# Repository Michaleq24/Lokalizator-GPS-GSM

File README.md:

Katalog zawiera dokumentację i pliki związane z projektem "Lokalizator GPS/GSM".

Autor: Michał Figołuszka  INF s.5 gr.2

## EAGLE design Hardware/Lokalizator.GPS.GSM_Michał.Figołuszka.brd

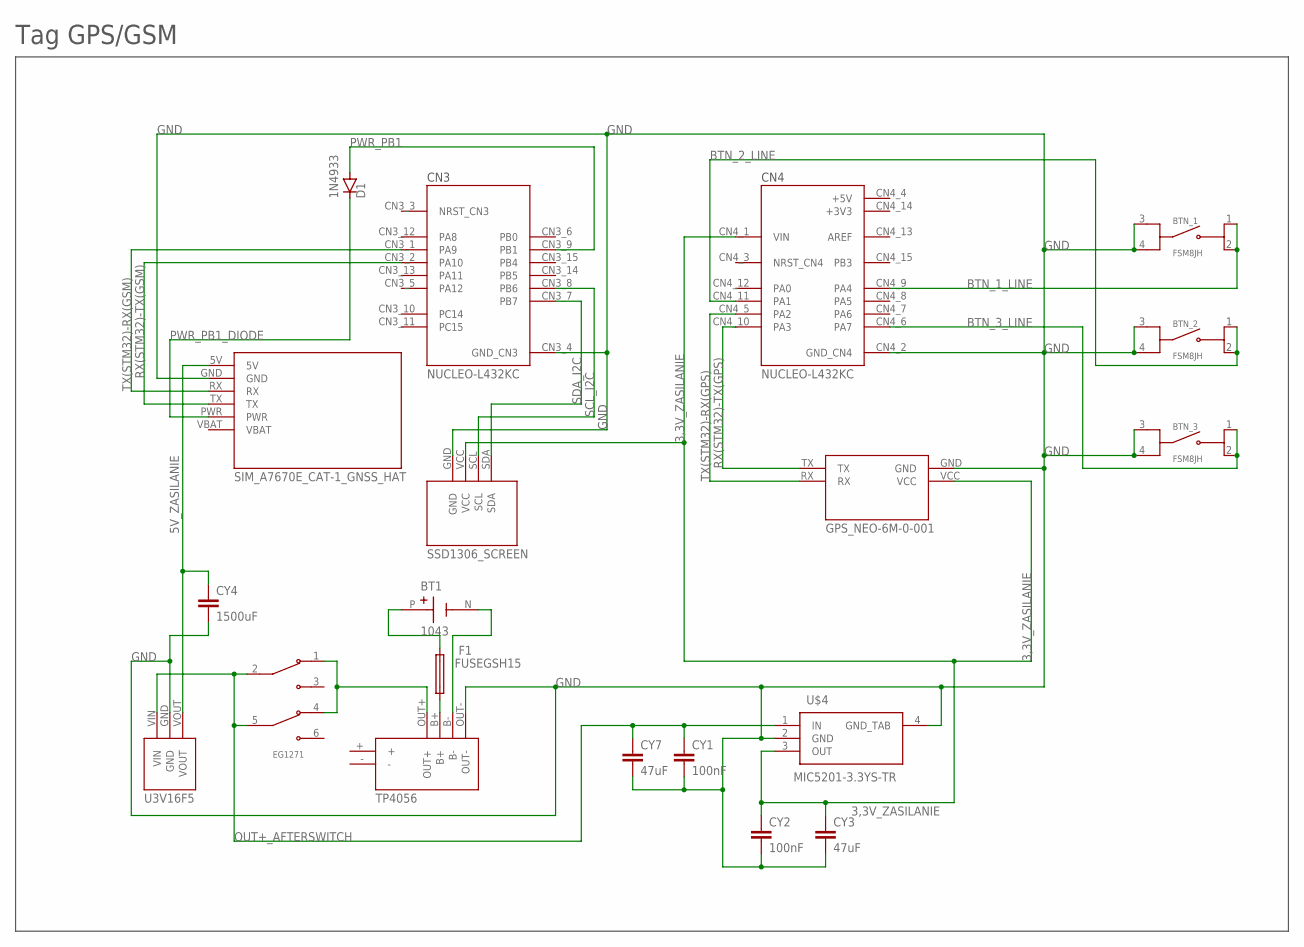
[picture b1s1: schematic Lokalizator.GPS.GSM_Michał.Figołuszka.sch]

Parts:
BT1: 1043; BAT_1043
BTN_1, BTN_2, BTN_3: FSM8JH; SW_FSM8JH
CY1, CY2: 100nF; YC7B5
CY3, CY7: 47uF; YC7B5
CY4: 1500uF; YC7B5
D1: 1N4933; DO41-10
F1: FUSEGSH15; GSH15
S1: EG1271; SW_EG1271
U1: NUCLEO-L432KC; MODULE_NUCLEO-L432KC
U$1: U3V16F5
U$2: TP4056
U$3: SSD1306_SCREEN
U$4: MIC5201-3.3YS-TR; SOT230P700X180-4N
U$6: SIM7020E_NB-IOT_HAT
U$7: GPS_NEO-6M-0-001

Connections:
3,3V_ZASILANIE: CY2.1, CY3.1, U1.CN4_1 (VIN), U$3.VCC, U$4.3 (OUT), U$7.VCC
5V_ZASILANIE: CY4.1, U$1.VOUT, U$6.5V
+3V3: U1.CN4_14 (+3V3)
+5V: U1.CN4_4 (+5V)
B+: BT1.P (POS), F1.2
B+_2: F1.1, U$2.B+
B-: BT1.N (NEG), U$2.B-
BTN_1_LINE: BTN_1.1 (NO_1), BTN_1.2 (NO_2), U1.CN4_9 (PA4)
BTN_2_LINE: BTN_2.1 (NO_1), BTN_2.2 (NO_2), U1.CN4_11 (PA1)
BTN_3_LINE: BTN_3.1 (NO_1), BTN_3.2 (NO_2), U1.CN4_6 (PA7)
GND: BTN_1.3 (COM_3), BTN_1.4 (COM_4), BTN_2.3 (COM_3), BTN_2.4 (COM_4), BTN_3.3 (COM_3), BTN_3.4 (COM_4), CY1.2, CY2.2, CY3.2, CY4.2, CY7.2, U1.CN3_4 (GND_CN3), U1.CN4_2 (GND_CN4), U$1.GND, U$2.OUT-, U$3.GND, U$4.2 (GND), U$4.4 (GND_TAB), U$6.GND, U$7.GND
OUT+: S1.1 (NC1), S1.4 (NC2), U$2.OUT+
OUT+_AFTERSWITCH: CY1.1, CY7.1, S1.2 (COM1), S1.5 (COM2), U$1.VIN, U$4.1 (IN)
PWR_PB1: D1.A, U1.CN3_9 (PB1)
PWR_PB1_DIODE: D1.C, U$6.PWR
RX(STM32)-TX(GPS): U1.CN4_10 (PA3), U$7.TX
RX(STM32)-TX(GSM): U1.CN3_2 (PA10), U$6.TX
SCL_I2C: U1.CN3_8 (PB6), U$3.SCL
SDA_I2C: U1.CN3_7 (PB7), U$3.SDA
TX(STM32)-RX(GPS): U1.CN4_5 (PA2), U$7.RX
TX(STM32)-RX(GSM): U1.CN3_1 (PA9), U$6.RX

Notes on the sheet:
Tag GPS/GSM

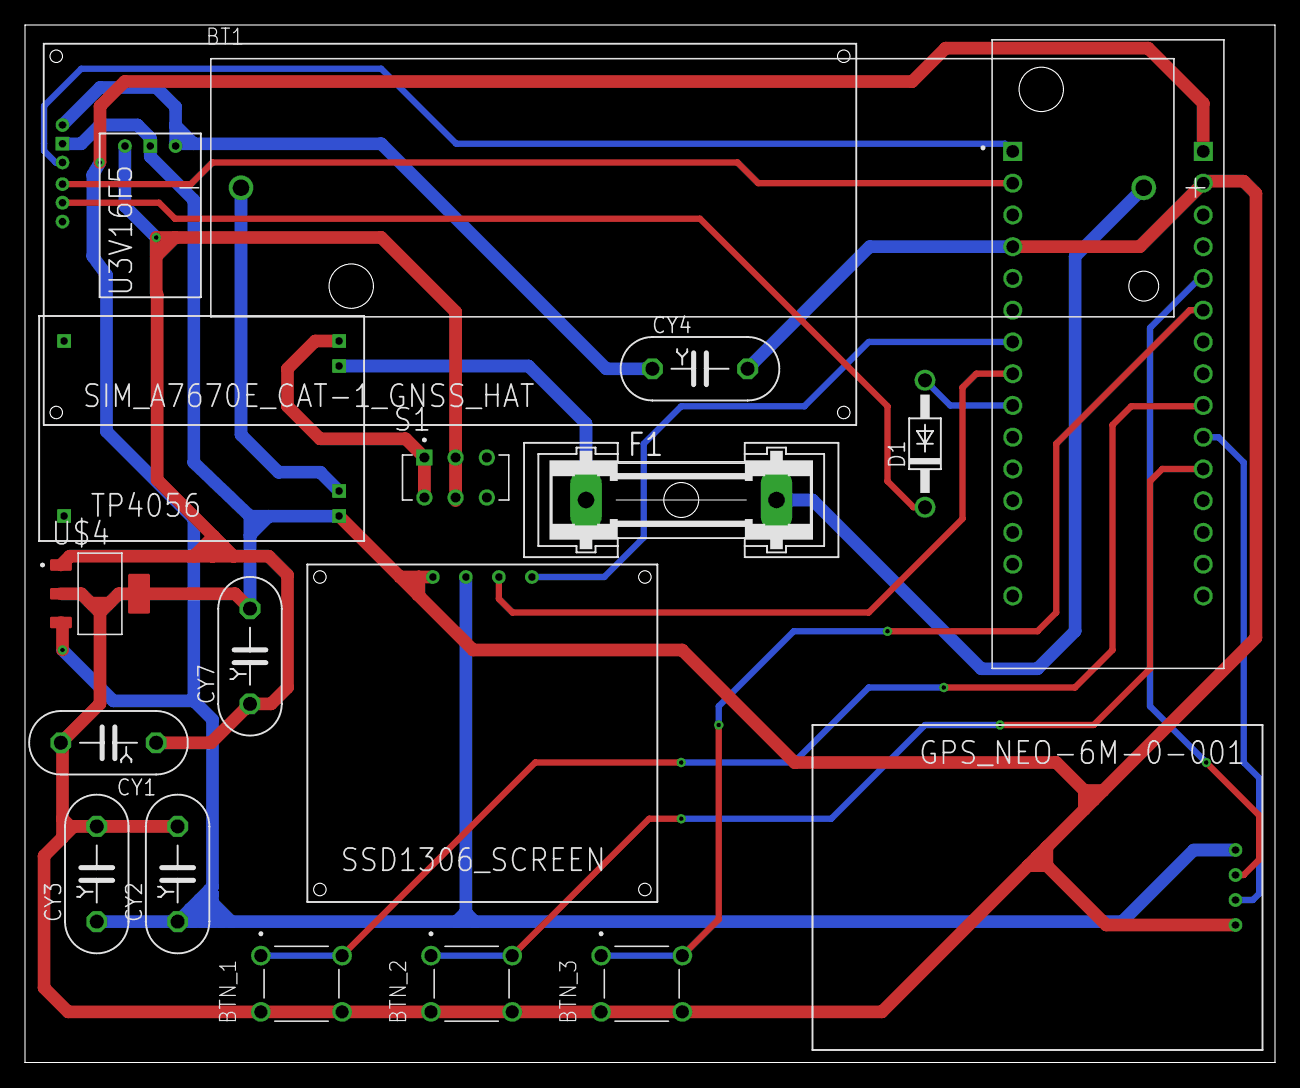
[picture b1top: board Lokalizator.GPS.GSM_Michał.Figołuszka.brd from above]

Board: 2 copper layers, 100.0 x 83.0 mm, 19 parts (0 on the bottom side), 19 nets.

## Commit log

2026-01-10 Dodano README.md
2026-01-10 Dodany projekt dla środowiska STM32CubeIDE
2026-01-10 Dodano zakładkę Software
2026-01-10 Dodano zakładkę Libraries_Michał.Figołuszka
2026-01-10 Dodano zakładkę Hardware
2026-01-10 Dodano zakładkę Dokumentacja
2026-01-14 Dodano Raport
